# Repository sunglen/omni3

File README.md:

omni3
====

AGV with three omni wheels, prototype

- gcc: firmware, gcc

- omni3v0-dist: firmware, Keil uVision

- doc: related documents

- pcb: Eagle Schematics, PCB and Gerber files

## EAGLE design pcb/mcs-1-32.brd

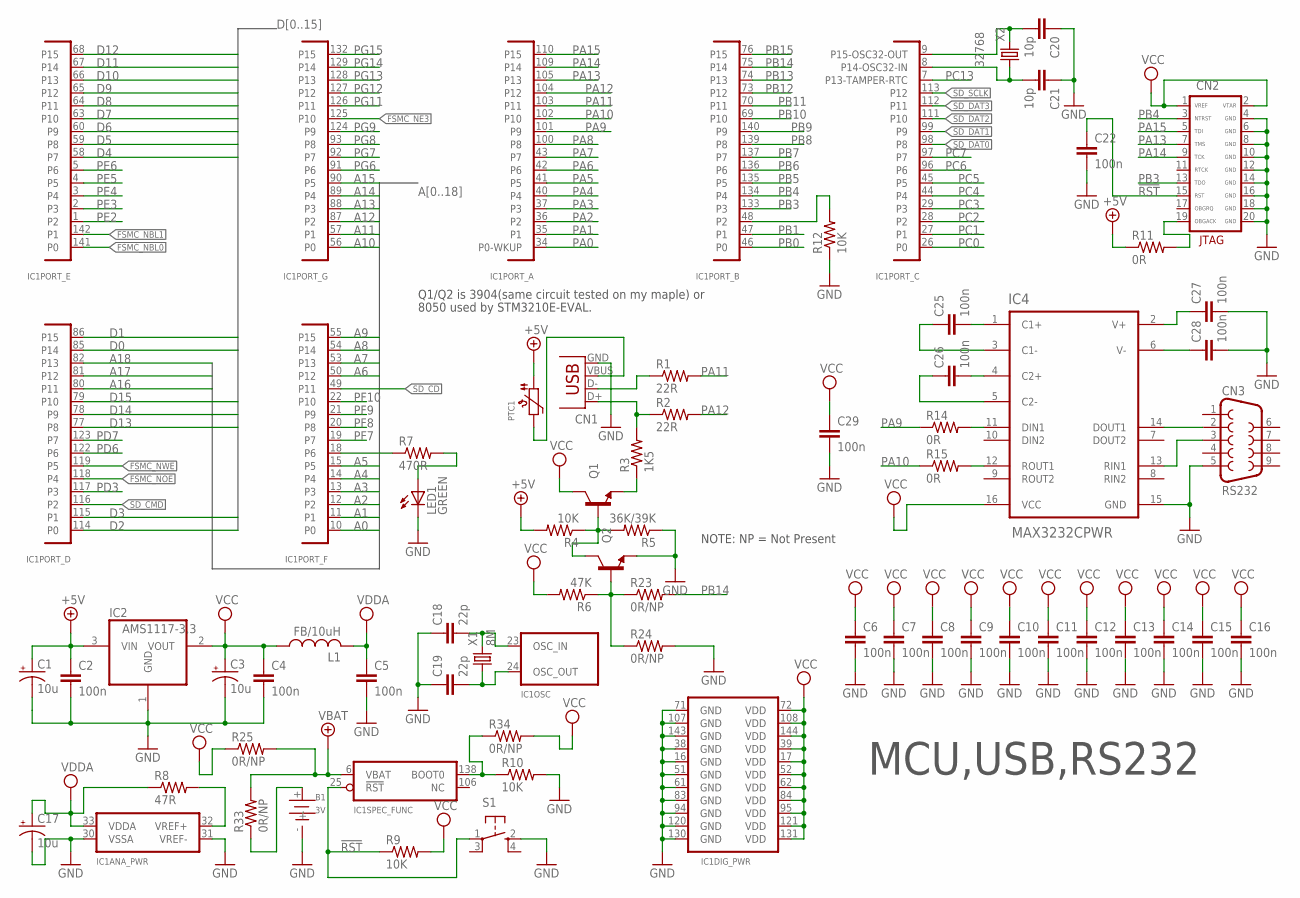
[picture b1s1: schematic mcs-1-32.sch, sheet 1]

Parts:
B1: 3V; 1220-SMD
C1, C3, C17: 10u; EIA3216
C2, C4, C5, C6, C7, C8, C9, C10, C11, C12, C13, C14, C15, C16, C22, C25, C26, C27, C28, C29: 100n; 0603-CAP
C18, C19: 22p; 0603-CAP
C20, C21: 10p; 0603-CAP
CN1: USBSMD; USB-MINIB
CN2: JTAG-ARM-HDR100; JTAG-ARM
CN3: RS232; DB9
IC1: STM32F103ZE; SQFP-S-20X20-144
IC2: AMS1117-3.3; BURR-BROWN_SOT223
IC4: MAX3232CPWR; SOP65P640X120-16N
L1: FB/10uH; L2012C
LED1: GREEN; CHIPLED_0805
PTC1: PTCPTC0805; PTC0805
Q1, Q2: TRANSISTOR_NPNSOT23-3; SOT23-3
R1, R2: 22R; 0603-RES
R3: 1K5; 0603-RES
R4, R9, R10, R12: 10K; 0603-RES
R5: 36K/39K; 0603-RES
R6: 47K; 0603-RES
R7: 470R; 0603-RES
R8: 47R; 0603-RES
R11, R14, R15: 0R; 0603-RES
R23, R24, R25, R33, R34: 0R/NP; 0603-RES
S1: SWITCH-TACT_SFKHHM
X1: 8M; HC49US
X2: 32768; CRYSTAL-32KHZ-3215

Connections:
!RST: C22.1, CN2.15 (RST), IC1.25 (!RST), R9.1, S1.1
+5V: C1.A (+), C2.1, IC2.3 (VIN), PTC1.1, R4.2, R11.1; also elsewhere on the board
A0: IC1.10 (P0); also elsewhere on the board
A1: IC1.11 (P1); also elsewhere on the board
A2: IC1.12 (P2); also elsewhere on the board
A3: IC1.13 (P3); also elsewhere on the board
A4: IC1.14 (P4); also elsewhere on the board
A5: IC1.15 (P5); also elsewhere on the board
A6: IC1.50 (P12); also elsewhere on the board
A7: IC1.53 (P13); also elsewhere on the board
A8: IC1.54 (P14); also elsewhere on the board
A9: IC1.55 (P15); also elsewhere on the board
A10: IC1.56 (P0); also elsewhere on the board
A11: IC1.57 (P1); also elsewhere on the board
A12: IC1.87 (P2); also elsewhere on the board
A13: IC1.88 (P3); also elsewhere on the board
A14: IC1.89 (P4); also elsewhere on the board
A15: IC1.90 (P5); also elsewhere on the board
A16: IC1.80 (P11); also elsewhere on the board
A17: IC1.81 (P12); also elsewhere on the board
A18: IC1.82 (P13); also elsewhere on the board
D0: IC1.85 (P14); also elsewhere on the board
D1: IC1.86 (P15); also elsewhere on the board
D2: IC1.114 (P0); also elsewhere on the board
D3: IC1.115 (P1); also elsewhere on the board
D4: IC1.58 (P7); also elsewhere on the board
D5: IC1.59 (P8); also elsewhere on the board
D6: IC1.60 (P9); also elsewhere on the board
D7: IC1.63 (P10); also elsewhere on the board
D8: IC1.64 (P11); also elsewhere on the board
D9: IC1.65 (P12); also elsewhere on the board
D10: IC1.66 (P13); also elsewhere on the board
D11: IC1.67 (P14); also elsewhere on the board
D12: IC1.68 (P15); also elsewhere on the board
D13: IC1.77 (P8); also elsewhere on the board
D14: IC1.78 (P9); also elsewhere on the board
D15: IC1.79 (P10); also elsewhere on the board
FSMC_NBL0: IC1.141 (P0); also elsewhere on the board
FSMC_NBL1: IC1.142 (P1); also elsewhere on the board
FSMC_NE3: IC1.125 (P10); also elsewhere on the board
FSMC_NOE: IC1.118 (P4); also elsewhere on the board
FSMC_NWE: IC1.119 (P5); also elsewhere on the board
GND: B1.-, C1.C (-), C2.2, C3.C (-), C4.2, C5.2, C6.2, C7.2, C8.2, C9.2, C10.2, C11.2, C12.2, C13.2, C14.2, C15.2, C16.2, C17.C (-), C18.1, C19.1, C20.1, C21.1, C22.2, C27.2, C28.2, C29.2, CN1.GND, CN2.4 (GND), CN2.6 (GND), CN2.8 (GND), CN2.10 (GND), CN2.12 (GND), CN2.14 (GND), CN2.16 (GND), CN2.18 (GND), CN2.20 (GND), CN3.5, IC1.16 (GND), IC1.30 (VSSA), IC1.31 (VREF-), IC1.38 (GND), IC1.51 (GND), IC1.61 (GND), IC1.71 (GND), IC1.83 (GND), IC1.94 (GND), IC1.107 (GND), IC1.120 (GND), IC1.130 (GND), IC1.143 (GND), IC2.1 (GND), IC4.15 (GND), LED1.C, Q2.2 (E), R5.1, R10.2, R12.1, R24.2, S1.2; also elsewhere on the board
unnamed: Q1.2 (E), R3.1
unnamed: Q1.1 (B), Q2.3 (C), R4.1, R5.2
unnamed: Q2.1 (B), R6.1, R23.1, R24.1
unnamed: CN1.D-, R1.1
unnamed: CN1.D+, R2.1, R3.2
unnamed: IC1.18 (P6), R7.1
unnamed: LED1.A, R7.2
unnamed: IC1.32 (VREF+), R8.2
unnamed: IC1.138 (BOOT0), R10.1, R34.1
unnamed: IC1.48 (P2), R12.2
unnamed: B1.+, R33.1
unnamed: C18.2, IC1.23 (OSC_IN), X1.2
unnamed: C19.2, IC1.24 (OSC_OUT), X1.1
unnamed: C20.2, IC1.9 (P15-OSC32-OUT), X2.2
unnamed: C21.2, IC1.8 (P14-OSC32-IN), X2.1
unnamed: CN2.19 (OBGACK), R11.2
unnamed: IC4.11 (DIN1), R14.2
unnamed: IC4.12 (ROUT1), R15.2
unnamed: CN1.VBUS, PTC1.2
unnamed: CN3.2, IC4.14 (DOUT1)
unnamed: CN3.3, IC4.13 (RIN1)
unnamed: C25.2, IC4.1 (C1+)
unnamed: C25.1, IC4.3 (C1-)
unnamed: C26.2, IC4.4 (C2+)
unnamed: C26.1, IC4.5 (C2-)
unnamed: C27.1, IC4.2 (V+)
unnamed: C28.1, IC4.6 (V-)
PA0: IC1.34 (P0-WKUP); also elsewhere on the board
PA1: IC1.35 (P1); also elsewhere on the board
PA2: IC1.36 (P2); also elsewhere on the board
PA3: IC1.37 (P3); also elsewhere on the board
PA4: IC1.40 (P4); also elsewhere on the board
PA5: IC1.41 (P5); also elsewhere on the board
PA6: IC1.42 (P6); also elsewhere on the board
PA7: IC1.43 (P7); also elsewhere on the board
PA8: IC1.100 (P8); also elsewhere on the board
PA9: IC1.101 (P9), R14.1
PA10: IC1.102 (P10), R15.1
PA11: IC1.103 (P11), R1.2
PA12: IC1.104 (P12), R2.2
PA13: CN2.7 (TMS), IC1.105 (P13)
PA14: CN2.9 (TCK), IC1.109 (P14)
PA15: CN2.5 (TDI), IC1.110 (P15)
PB0: IC1.46 (P0); also elsewhere on the board
PB1: IC1.47 (P1); also elsewhere on the board
PB3: CN2.13 (TDO), IC1.133 (P3)
PB4: CN2.3 (NTRST), IC1.134 (P4)
PB5: IC1.135 (P5); also elsewhere on the board
PB6: IC1.136 (P6); also elsewhere on the board
PB7: IC1.137 (P7); also elsewhere on the board
PB8: IC1.139 (P8); also elsewhere on the board
PB9: IC1.140 (P9); also elsewhere on the board
PB10: IC1.69 (P10); also elsewhere on the board
PB11: IC1.70 (P11); also elsewhere on the board
PB12: IC1.73 (P12); also elsewhere on the board
PB13: IC1.74 (P13); also elsewhere on the board
PB14: IC1.75 (P14), R23.2; also elsewhere on the board
PB15: IC1.76 (P15); also elsewhere on the board
PC0: IC1.26 (P0); also elsewhere on the board
PC1: IC1.27 (P1); also elsewhere on the board
PC2: IC1.28 (P2); also elsewhere on the board
PC3: IC1.29 (P3); also elsewhere on the board
PC4: IC1.44 (P4); also elsewhere on the board
PC5: IC1.45 (P5); also elsewhere on the board
PC6: IC1.96 (P6); also elsewhere on the board
PC7: IC1.97 (P7); also elsewhere on the board
PC13: IC1.7 (P13-TAMPER-RTC); also elsewhere on the board
PD3: IC1.117 (P3); also elsewhere on the board
PD6: IC1.122 (P6); also elsewhere on the board
PD7: IC1.123 (P7); also elsewhere on the board
PE2: IC1.1 (P2); also elsewhere on the board
PE3: IC1.2 (P3); also elsewhere on the board
PE4: IC1.3 (P4); also elsewhere on the board
PE5: IC1.4 (P5); also elsewhere on the board
PE6: IC1.5 (P6); also elsewhere on the board
PF7: IC1.19 (P7); also elsewhere on the board
PF8: IC1.20 (P8); also elsewhere on the board
PF9: IC1.21 (P9); also elsewhere on the board
PF10: IC1.22 (P10); also elsewhere on the board
PG6: IC1.91 (P6); also elsewhere on the board
PG7: IC1.92 (P7); also elsewhere on the board
PG8: IC1.93 (P8); also elsewhere on the board
PG9: IC1.124 (P9); also elsewhere on the board
PG11: IC1.126 (P11); also elsewhere on the board
PG12: IC1.127 (P12); also elsewhere on the board
PG13: IC1.128 (P13); also elsewhere on the board
PG14: IC1.129 (P14); also elsewhere on the board
PG15: IC1.132 (P15); also elsewhere on the board
SD_CD: IC1.49 (P11); also elsewhere on the board
SD_CMD: IC1.116 (P2); also elsewhere on the board
SD_DAT0: IC1.98 (P8); also elsewhere on the board
SD_DAT1: IC1.99 (P9); also elsewhere on the board
SD_DAT2: IC1.111 (P10); also elsewhere on the board
SD_DAT3: IC1.112 (P11); also elsewhere on the board
SD_SCLK: IC1.113 (P12); also elsewhere on the board
VBAT: IC1.6 (VBAT), R25.2, R33.2
VCC: C3.A (+), C4.1, C6.1, C7.1, C8.1, C9.1, C10.1, C11.1, C12.1, C13.1, C14.1, C15.1, C16.1, C29.1, CN2.1 (VREF), CN2.2 (VTAR), IC1.17 (VDD), IC1.39 (VDD), IC1.52 (VDD), IC1.62 (VDD), IC1.72 (VDD), IC1.84 (VDD), IC1.95 (VDD), IC1.108 (VDD), IC1.121 (VDD), IC1.131 (VDD), IC1.144 (VDD), IC2.2 (VOUT), IC4.16 (VCC), L1.1, Q1.3 (C), R6.2, R9.2, R25.1, R34.2; also elsewhere on the board
VDDA: C5.1, C17.A (+), IC1.33 (VDDA), L1.2, R8.1

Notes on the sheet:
Q1/Q2 is 3904(same circuit tested on my maple) or
8050 used by STM3210E-EVAL.
MCU,USB,RS232
NOTE: NP = Not Present

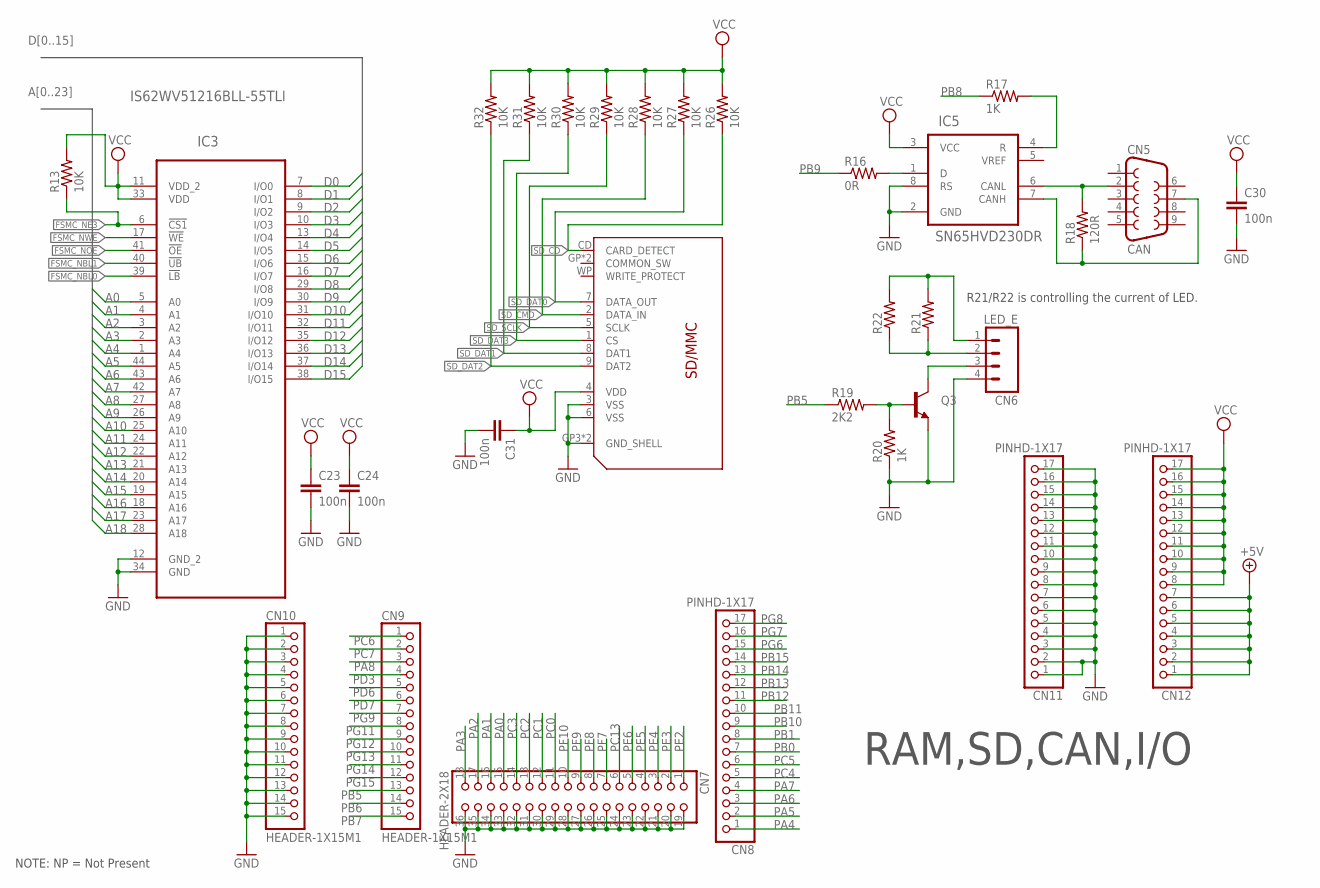
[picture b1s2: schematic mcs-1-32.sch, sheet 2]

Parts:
C23, C24, C30, C31: 100n; 0603-CAP
CN4: SDMMC06132; 06132
CN5: CAN; DB9_MALE
CN6: LED_E; 1X04_NS
CN7: HEADER-2X18; 2X18U
CN8, CN11, CN12: PINHD-1X17; 1X17M1
CN9, CN10: HEADER-1X15M1; 1X15M1
IC3: IS62WV51216BLL-55TLI; SOP80P1176X120-44N
IC5: SN65HVD230DR; SOIC127P600X175-8N
Q3: TRANSISTOR_NPNSOT23-3; SOT23-3
R13, R26, R27, R28, R29, R30, R31, R32: 10K; 0603-RES
R16: 0R; 0603-RES
R17, R20: 1K; 0603-RES
R18: 120R; 0603-RES
R19: 2K2; 0603-RES
R21, R22: RESISTOR0603-RES; 0603-RES

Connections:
+5V: CN12.1, CN12.2, CN12.3, CN12.4, CN12.5, CN12.6, CN12.7; also elsewhere on the board
A0: IC3.5 (A0); also elsewhere on the board
A1: IC3.4 (A1); also elsewhere on the board
A2: IC3.3 (A2); also elsewhere on the board
A3: IC3.2 (A3); also elsewhere on the board
A4: IC3.1 (A4); also elsewhere on the board
A5: IC3.44 (A5); also elsewhere on the board
A6: IC3.43 (A6); also elsewhere on the board
A7: IC3.42 (A7); also elsewhere on the board
A8: IC3.27 (A8); also elsewhere on the board
A9: IC3.26 (A9); also elsewhere on the board
A10: IC3.25 (A10); also elsewhere on the board
A11: IC3.24 (A11); also elsewhere on the board
A12: IC3.22 (A12); also elsewhere on the board
A13: IC3.21 (A13); also elsewhere on the board
A14: IC3.20 (A14); also elsewhere on the board
A15: IC3.19 (A15); also elsewhere on the board
A16: IC3.18 (A16); also elsewhere on the board
A17: IC3.23 (A17); also elsewhere on the board
A18: IC3.28 (A18); also elsewhere on the board
D0: IC3.7 (I/O0); also elsewhere on the board
D1: IC3.8 (I/O1); also elsewhere on the board
D2: IC3.9 (I/O2); also elsewhere on the board
D3: IC3.10 (I/O3); also elsewhere on the board
D4: IC3.13 (I/O4); also elsewhere on the board
D5: IC3.14 (I/O5); also elsewhere on the board
D6: IC3.15 (I/O6); also elsewhere on the board
D7: IC3.16 (I/O7); also elsewhere on the board
D8: IC3.29 (I/O8); also elsewhere on the board
D9: IC3.30 (I/O9); also elsewhere on the board
D10: IC3.31 (I/O10); also elsewhere on the board
D11: IC3.32 (I/O11); also elsewhere on the board
D12: IC3.35 (I/O12); also elsewhere on the board
D13: IC3.36 (I/O13); also elsewhere on the board
D14: IC3.37 (I/O14); also elsewhere on the board
D15: IC3.38 (I/O15); also elsewhere on the board
FSMC_NBL0: IC3.39 (!LB); also elsewhere on the board
FSMC_NBL1: IC3.40 (!UB); also elsewhere on the board
FSMC_NE3: IC3.6 (!CS1), R13.1; also elsewhere on the board
FSMC_NOE: IC3.41 (!OE); also elsewhere on the board
FSMC_NWE: IC3.17 (!WE); also elsewhere on the board
GND: C23.2, C24.2, C30.2, C31.2, CN4.3 (VSS), CN4.6 (VSS), CN4.GP3 (GND_SHELL), CN4.GP4 (GND_SHELL), CN6.4, CN7.19, CN7.20, CN7.21, CN7.22, CN7.23, CN7.24, CN7.25, CN7.26, CN7.27, CN7.28, CN7.29, CN7.30, CN7.31, CN7.32, CN7.33, CN7.34, CN7.35, CN7.36, CN10.1, CN10.2, CN10.3, CN10.4, CN10.5, CN10.6, CN10.7, CN10.8, CN10.9, CN10.10, CN10.11, CN10.12, CN10.13, CN10.14, CN10.15, CN11.1, CN11.2, CN11.3, CN11.4, CN11.5, CN11.6, CN11.7, CN11.8, CN11.9, CN11.10, CN11.11, CN11.12, CN11.13, CN11.14, CN11.15, CN11.16, CN11.17, IC3.12 (GND_2), IC3.34 (GND), IC5.2 (GND), IC5.8 (RS), Q3.2 (E), R20.1; also elsewhere on the board
unnamed: IC5.1 (D), R16.2
unnamed: IC5.4 (R), R17.2
unnamed: CN5.2, IC5.6 (CANL), R18.2
unnamed: CN5.7, IC5.7 (CANH), R18.1
unnamed: Q3.1 (B), R19.2, R20.2
unnamed: CN6.1, R21.2, R22.2
unnamed: CN6.2, R21.1, R22.1
unnamed: CN6.3, Q3.3 (C)
PA0: CN7.15; also elsewhere on the board
PA1: CN7.16; also elsewhere on the board
PA2: CN7.17; also elsewhere on the board
PA3: CN7.18; also elsewhere on the board
PA4: CN8.1; also elsewhere on the board
PA5: CN8.2; also elsewhere on the board
PA6: CN8.3; also elsewhere on the board
PA7: CN8.4; also elsewhere on the board
PA8: CN9.3; also elsewhere on the board
PB0: CN8.7; also elsewhere on the board
PB1: CN8.8; also elsewhere on the board
PB5: CN9.13, R19.1; also elsewhere on the board
PB6: CN9.14; also elsewhere on the board
PB7: CN9.15; also elsewhere on the board
PB8: R17.1; also elsewhere on the board
PB9: R16.1; also elsewhere on the board
PB10: CN8.9; also elsewhere on the board
PB11: CN8.10; also elsewhere on the board
PB12: CN8.11; also elsewhere on the board
PB13: CN8.12; also elsewhere on the board
PB14: CN8.13; also elsewhere on the board
PB15: CN8.14; also elsewhere on the board
PC0: CN7.11; also elsewhere on the board
PC1: CN7.12; also elsewhere on the board
PC2: CN7.13; also elsewhere on the board
PC3: CN7.14; also elsewhere on the board
PC4: CN8.5; also elsewhere on the board
PC5: CN8.6; also elsewhere on the board
PC6: CN9.1; also elsewhere on the board
PC7: CN9.2; also elsewhere on the board
PC13: CN7.6; also elsewhere on the board
PD3: CN9.4; also elsewhere on the board
PD6: CN9.5; also elsewhere on the board
PD7: CN9.6; also elsewhere on the board
PE2: CN7.1; also elsewhere on the board
PE3: CN7.2; also elsewhere on the board
PE4: CN7.3; also elsewhere on the board
PE5: CN7.4; also elsewhere on the board
PE6: CN7.5; also elsewhere on the board
PF7: CN7.7; also elsewhere on the board
PF8: CN7.8; also elsewhere on the board
PF9: CN7.9; also elsewhere on the board
PF10: CN7.10; also elsewhere on the board
PG6: CN8.15; also elsewhere on the board
PG7: CN8.16; also elsewhere on the board
PG8: CN8.17; also elsewhere on the board
PG9: CN9.7; also elsewhere on the board
PG11: CN9.8; also elsewhere on the board
PG12: CN9.9; also elsewhere on the board
PG13: CN9.10; also elsewhere on the board
PG14: CN9.11; also elsewhere on the board
PG15: CN9.12; also elsewhere on the board
SD_CD: CN4.CD (CARD_DETECT), R26.1; also elsewhere on the board
SD_CMD: CN4.2 (DATA_IN), R28.1; also elsewhere on the board
SD_DAT0: CN4.7 (DATA_OUT), R27.1; also elsewhere on the board
SD_DAT1: CN4.8 (DAT1), R31.1; also elsewhere on the board
SD_DAT2: CN4.9 (DAT2), R32.1; also elsewhere on the board
SD_DAT3: CN4.1 (CS), R30.1; also elsewhere on the board
SD_SCLK: CN4.5 (SCLK), R29.1; also elsewhere on the board
VCC: C23.1, C24.1, C30.1, C31.1, CN4.4 (VDD), CN12.8, CN12.9, CN12.10, CN12.11, CN12.12, CN12.13, CN12.14, CN12.15, CN12.16, CN12.17, IC3.11 (VDD_2), IC3.33 (VDD), IC5.3 (VCC), R13.2, R26.2, R27.2, R28.2, R29.2, R30.2, R31.2, R32.2; also elsewhere on the board

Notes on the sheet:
NOTE: NP = Not Present
RAM,SD,CAN,I/O
R21/R22 is controlling the current of LED.

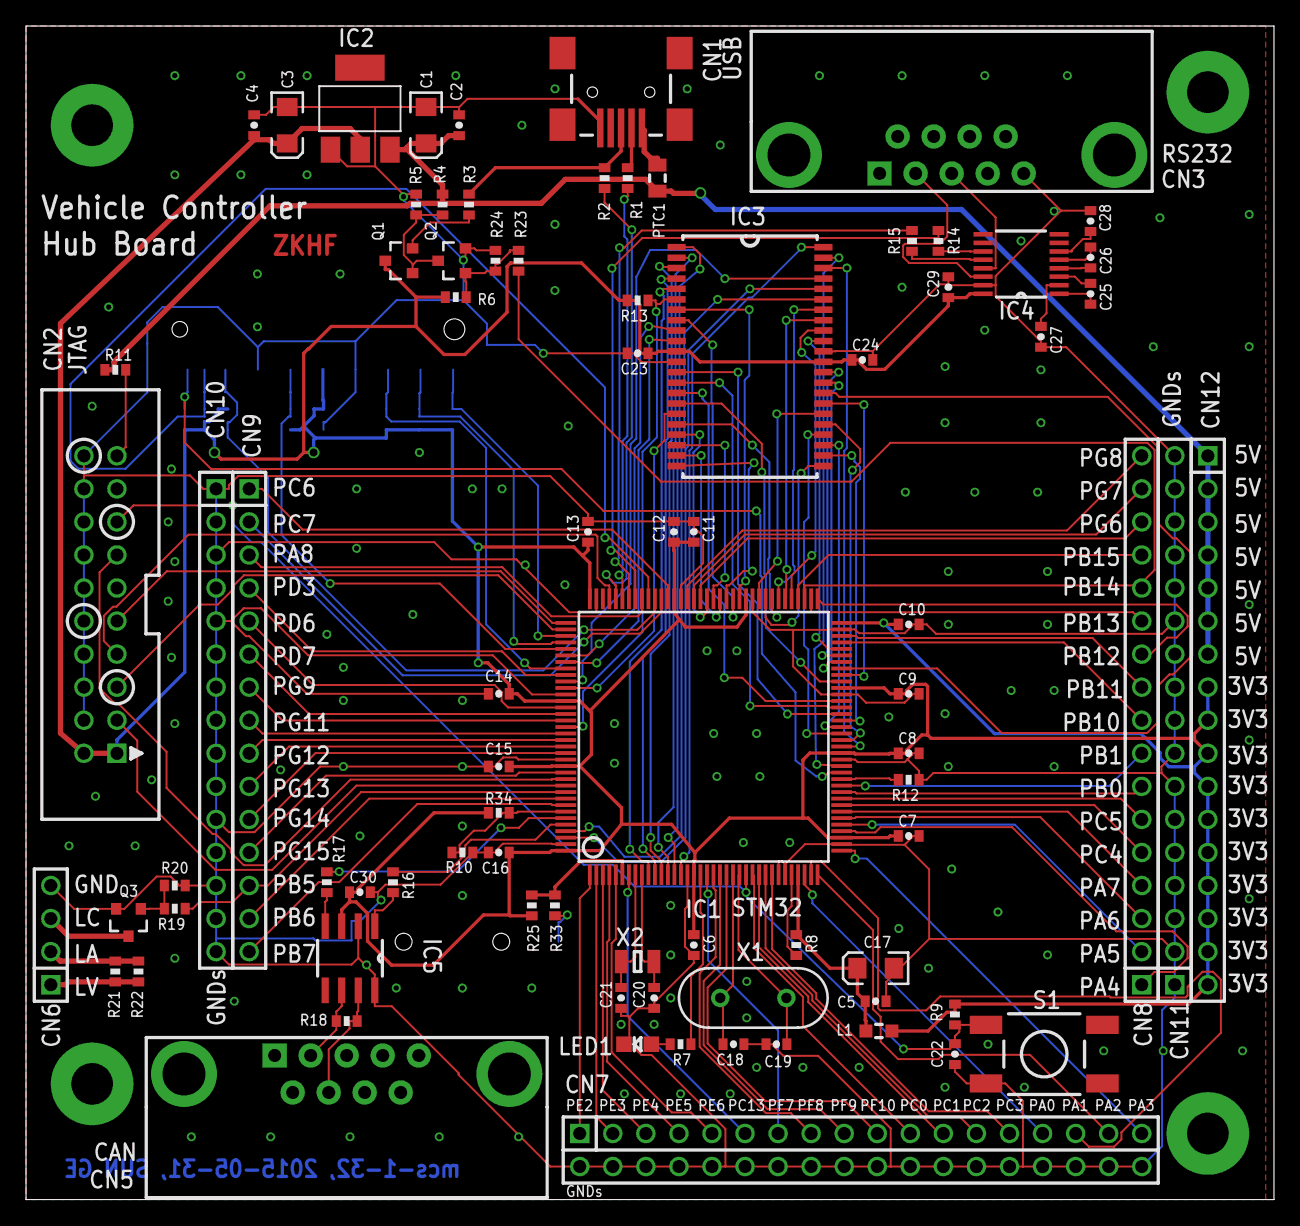
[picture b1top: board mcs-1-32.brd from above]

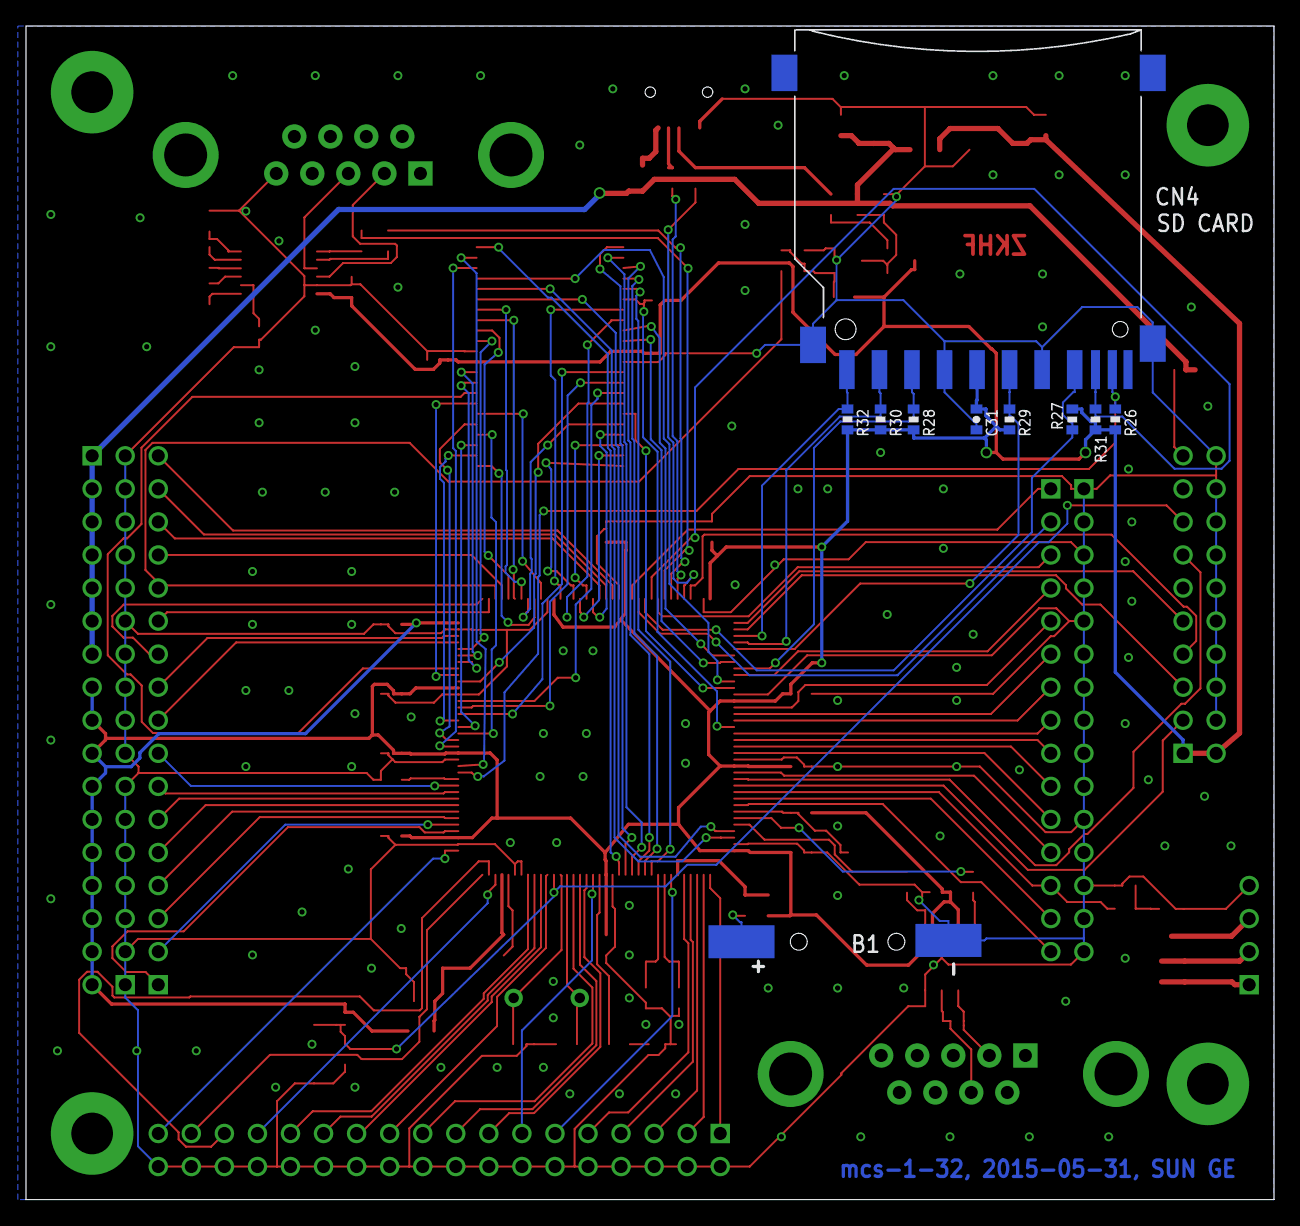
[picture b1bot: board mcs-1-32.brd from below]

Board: 2 copper layers, 95.9 x 90.2 mm, 92 parts (10 on the bottom side), 149 nets.

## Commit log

2017-11-22 add doc and pcb
2018-05-24 add openocd config file
